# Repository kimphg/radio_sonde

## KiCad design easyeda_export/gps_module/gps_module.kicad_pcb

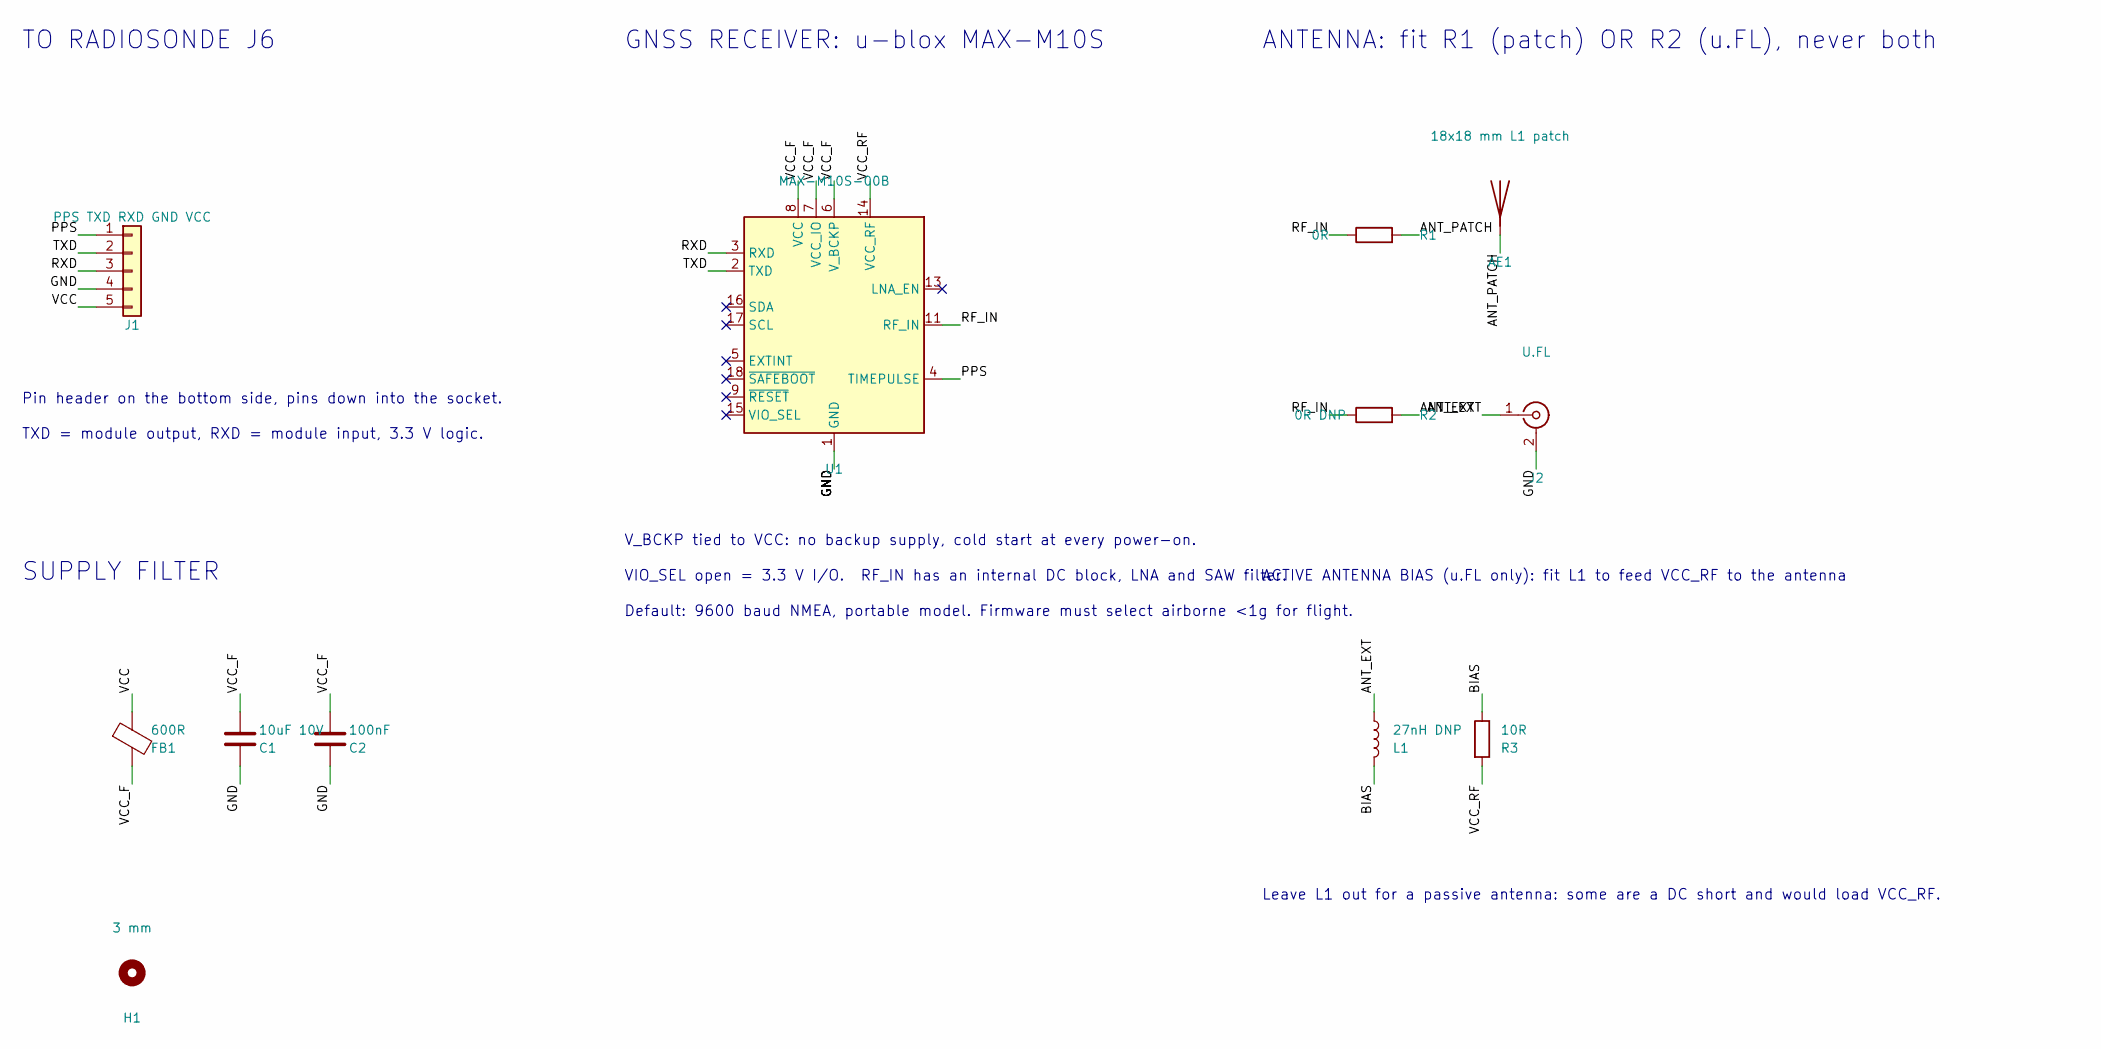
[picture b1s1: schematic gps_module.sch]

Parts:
AE1: 18x18 mm L1 patch; Patch_18x18_TH; MPN BWGNSCNX18-18W4; LCSC C784395
C1: 10uF 10V; C_0805_2012Metric; MPN CL21B106KOQNNNE; LCSC C95841
C2: 100nF; C_0603_1608Metric; MPN CL10B104KB8NNNC; LCSC C1591
FB1: 600R; L_0603_1608Metric; MPN BLM18AG601SN1D; LCSC C19330
H1: 3 mm; MountingHole_3mm
J1: PPS TXD RXD GND VCC; PinHeader_1x05_P2.54mm_Vertical
J2: U.FL; U.FL_Hirose_U.FL-R-SMT-1_Vertical; MPN U.FL-R-SMT-1(80); LCSC C88374
L1: 27nH DNP; L_0603_1608Metric
R1: 0R; R_0603_1608Metric
R2: 0R DNP; R_0603_1608Metric
R3: 10R; R_0603_1608Metric
U1: MAX-M10S-00B; ublox_MAX; MPN MAX-M10S-00B; LCSC C4153167

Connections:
ANT_EXT: J2.1 (In), L1.1, R2.2
ANT_PATCH: AE1.1, R1.2
BIAS: L1.2, R3.1
GND: C1.2, C2.2, J1.4, J2.2 (Ext), U1.1 (GND), U1.10 (GND), U1.12 (GND)
PPS: J1.1, U1.4 (TIMEPULSE)
RF_IN: R1.1, R2.1, U1.11 (RF_IN)
RXD: J1.3, U1.3 (RXD)
TXD: J1.2, U1.2 (TXD)
VCC: FB1.1, J1.5
VCC_F: C1.1, C2.1, FB1.2, U1.6 (V_BCKP), U1.7 (VCC_IO), U1.8 (VCC)
VCC_RF: R3.2, U1.14 (VCC_RF)

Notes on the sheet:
TO RADIOSONDE J6
Pin header on the bottom side, pins down into the socket.
TXD = module output, RXD = module input, 3.3 V logic.
SUPPLY FILTER
GNSS RECEIVER: u-blox MAX-M10S
V_BCKP tied to VCC: no backup supply, cold start at every power-on.
VIO_SEL open = 3.3 V I/O. RF_IN has an internal DC block, LNA and SAW filter.
Default: 9600 baud NMEA, portable model. Firmware must select airborne <1g for flight.
ANTENNA: fit R1 (patch) OR R2 (u.FL), never both
ACTIVE ANTENNA BIAS (u.FL only): fit L1 to feed VCC_RF to the antenna
Leave L1 out for a passive antenna: some are a DC short and would load VCC_RF.

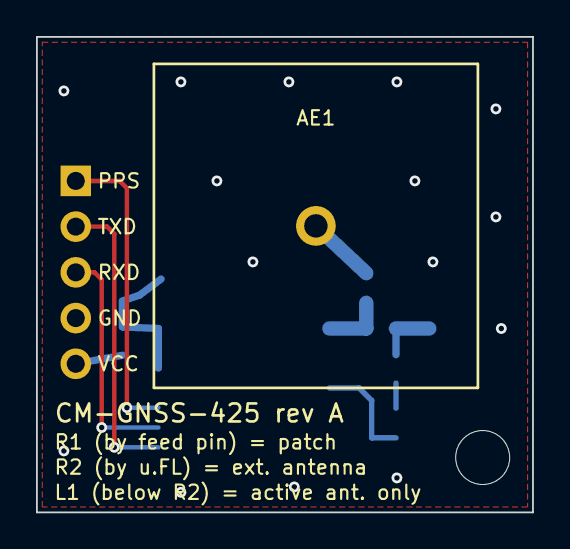
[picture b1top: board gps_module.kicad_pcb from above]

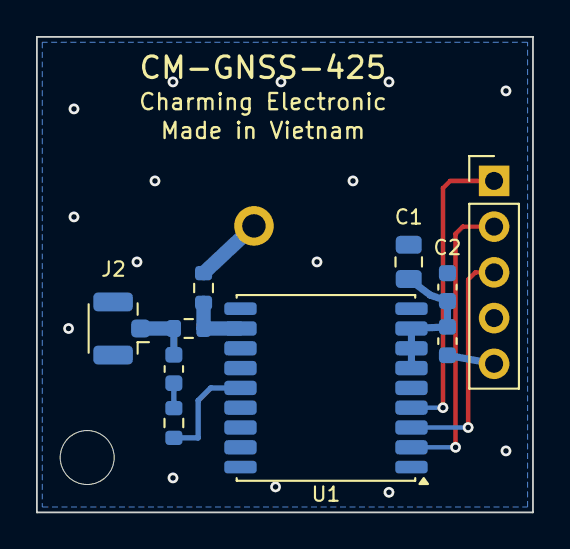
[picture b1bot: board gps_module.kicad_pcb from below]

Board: 2 copper layers, 27.6 x 26.4 mm, 12 parts (10 on the bottom side), 11 nets.

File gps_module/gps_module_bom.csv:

Designator,Quantity,Value,Footprint,LCSC Part Number,Manufacturer Part Number,Fit
U1,1,MAX-M10S-00B,ublox_MAX,C4153167,MAX-M10S-00B,yes
AE1,1,18x18x4 mm GPS L1 patch (through-hole pin),Patch_18x18_TH,C784395,BWGNSCNX18-18W4,yes (hand solder)
J1,1,Pin header 1x5 2.54 mm,PinHeader_1x05_P2.54mm_Vertical,,,yes (hand solder on bottom side)
J2,1,U.FL,U.FL_Hirose_U.FL-R-SMT-1,C88374,U.FL-R-SMT-1(80),yes
FB1,1,600R ferrite,0603,C19330,BLM18AG601SN1D,yes
C1,1,10uF 10V,0805,C95841,CL21B106KOQNNNE,yes
C2,1,100nF,0603,C1591,CL10B104KB8NNNC,yes
R1,1,0R,0603,,,yes (patch antenna selected)
R2,1,0R,0603,,,no (fit instead of R1 for u.FL)
R3,1,10R,0603,,,yes
L1,1,27nH,0603,,,no (fit only for an active antenna)

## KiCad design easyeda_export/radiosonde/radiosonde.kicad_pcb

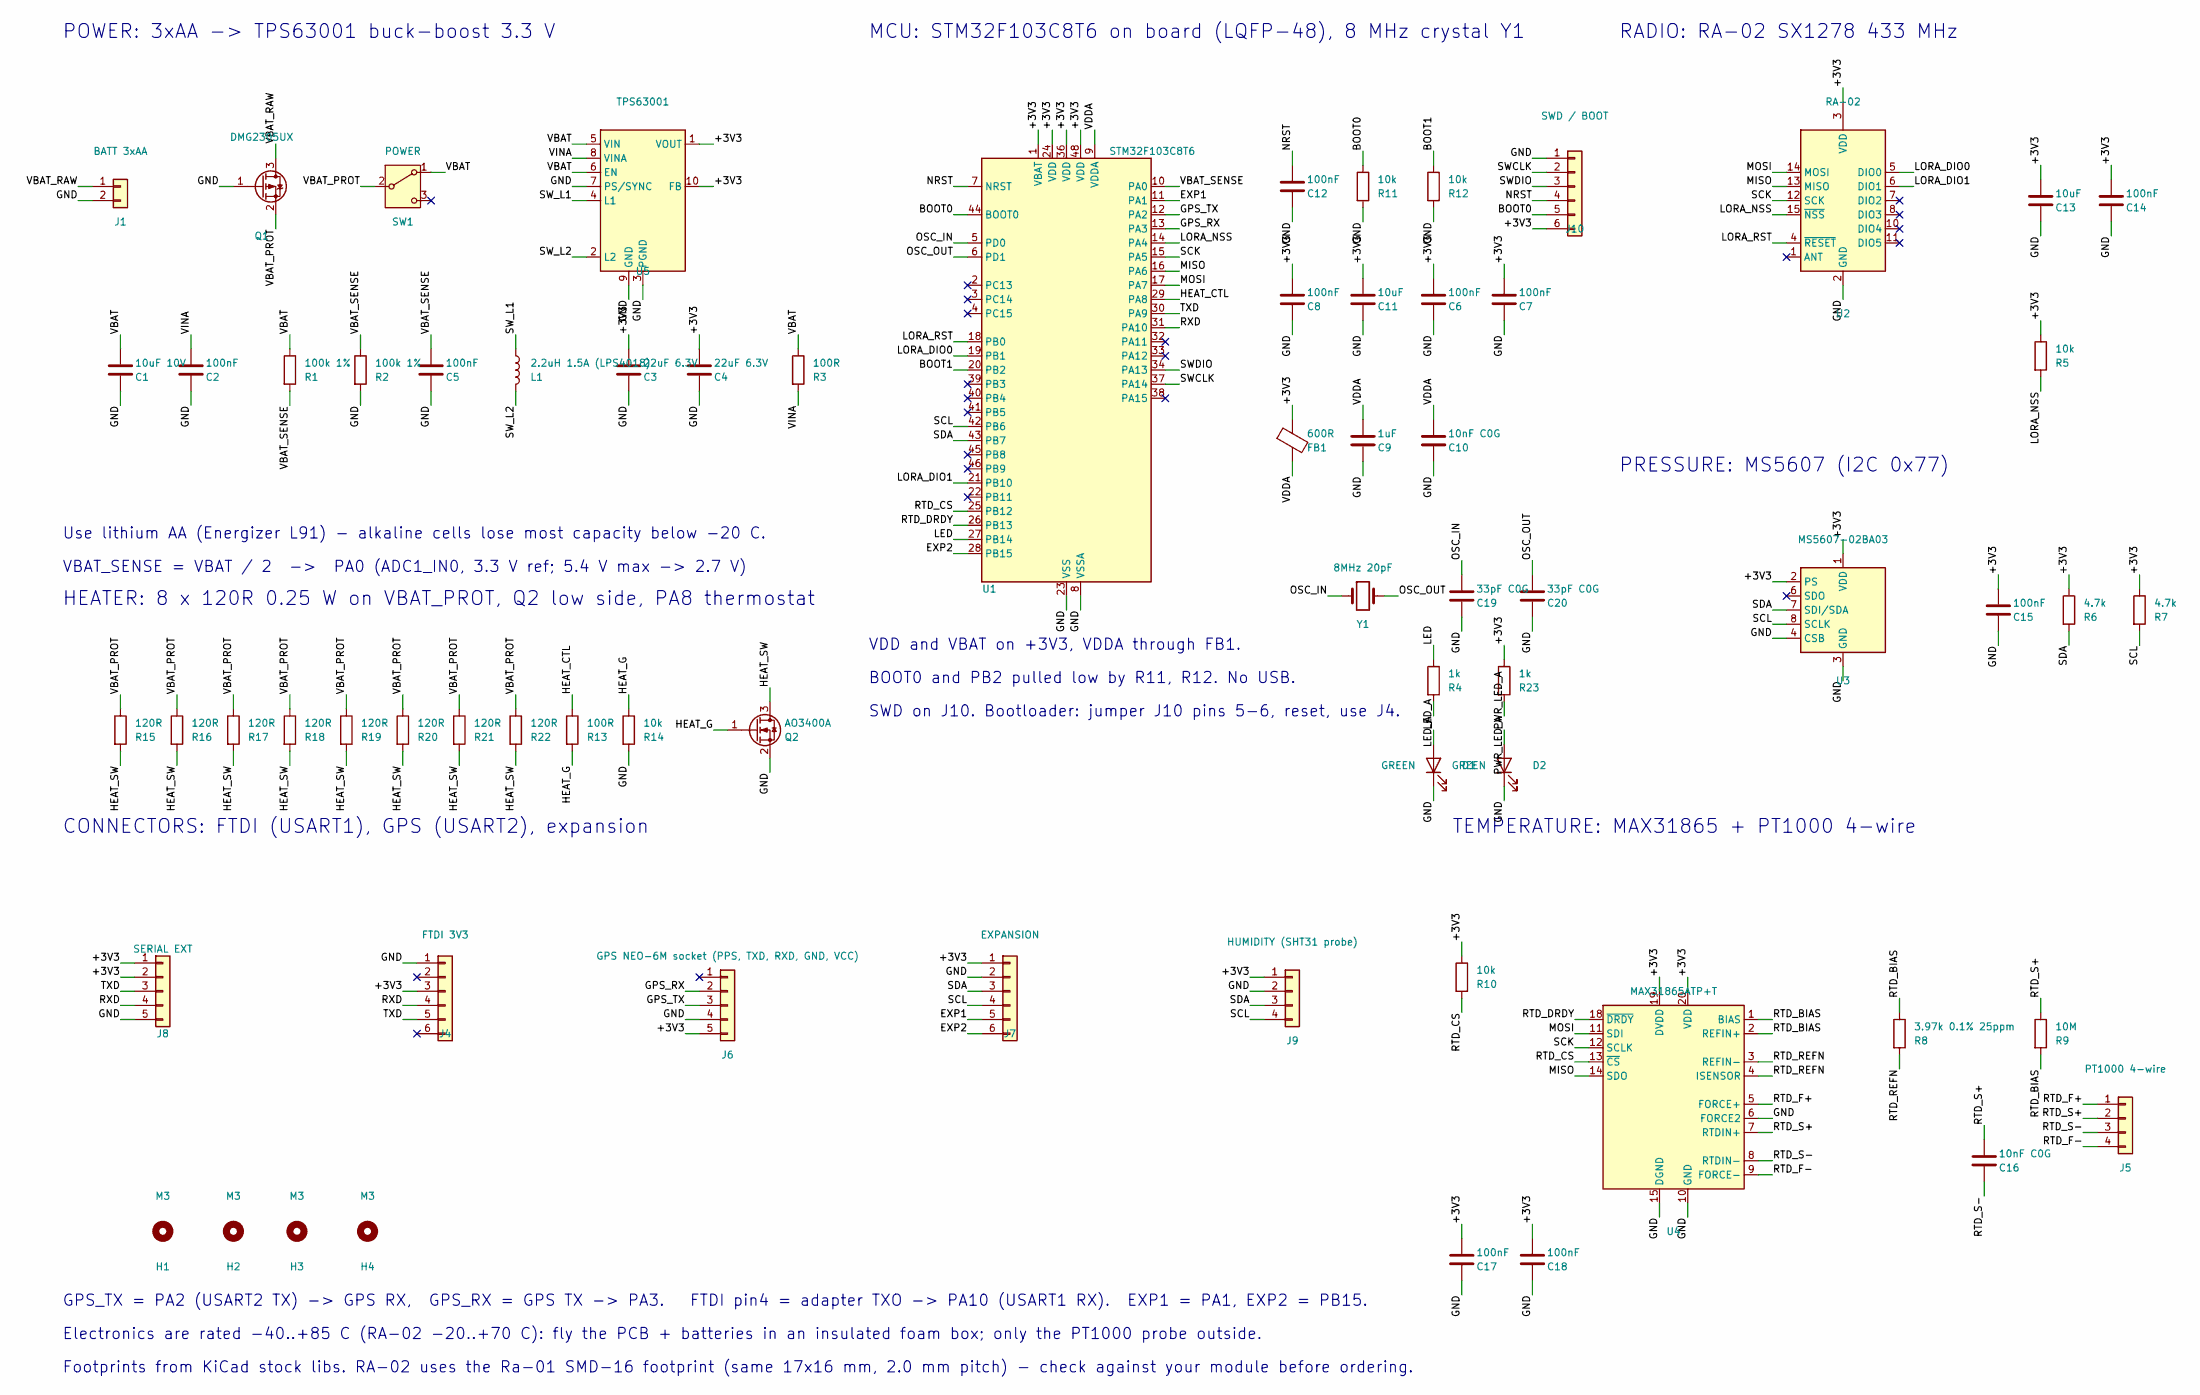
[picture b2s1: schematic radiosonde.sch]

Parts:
C1: 10uF 10V; C_0805_2012Metric; MPN CL21B106KOQNNNE; LCSC C95841
C2, C5, C6, C7, C8, C12, C14, C15, C17, C18: 100nF; C_0603_1608Metric; MPN CL10B104KB8NNNC; LCSC C1591
C3, C4: 22uF 6.3V; C_0805_2012Metric; MPN CL21A226MQQNNNE; LCSC C5674
C9: 1uF; C_0603_1608Metric; MPN CL10A105KB8NNNC; LCSC C15849
C10, C16: 10nF C0G; C_0603_1608Metric; MPN CGA3E1C0G2A103JT0Y0E; LCSC C432938
C11, C13: 10uF; C_0805_2012Metric; MPN CL21B106KOQNNNE; LCSC C95841
C19, C20: 33pF C0G; C_0603_1608Metric; MPN CL10C330JB8NNNC; LCSC C1663
D1, D2: GREEN; LED_0603_1608Metric; MPN 19-217/G7C-AN1P2/6T; LCSC C2986030
FB1: 600R; L_0603_1608Metric; MPN BLM18AG601SN1D; LCSC C19330
H1, H2, H3, H4: M3; MountingHole_3.2mm_M3
J1: BATT 3xAA; JST_PH_S2B-PH-K_1x02_P2.00mm_Horizontal; MPN S2B-PH-K-S(LF)(SN); LCSC C173752
J4: FTDI 3V3; PinHeader_1x06_P2.54mm_Vertical; MPN 2.54-1x6P; LCSC C37208
J5: PT1000 4-wire; JST_PH_B4B-PH-K_1x04_P2.00mm_Vertical; MPN B4B-PH-K-S(LF)(SN); LCSC C131334
J6: GPS NEO-6M socket (PPS, TXD, RXD, GND, VCC); GPS_NEO6M_5pin; MPN DS1023-1x5SF11; LCSC C7509517
J7: EXPANSION; PinHeader_1x06_P2.54mm_Vertical; MPN 2.54-1x6P; LCSC C37208
J8: SERIAL EXT; PinHeader_1x05_P2.54mm_Vertical
J9: HUMIDITY (SHT31 probe); JST_PH_B4B-PH-K_1x04_P2.00mm_Vertical; MPN B4B-PH-K-S(LF)(SN); LCSC C131334
J10: SWD / BOOT; PinHeader_1x06_P2.54mm_Vertical; MPN 2.54-1x6P; LCSC C37208
L1: 2.2uH 1.5A (LPS4018); L_Coilcraft_LPS4018; MPN LPS4018-222MRC; LCSC C4354938
Q1: DMG2305UX; SOT-23; MPN DMG2305UX-7; LCSC C150470
Q2: AO3400A; SOT-23; MPN AO3400A; LCSC C20917
R1, R2: 100k 1%; R_0603_1608Metric; MPN 0603WAF1003T5E; LCSC C25803
R3, R13: 100R; R_0603_1608Metric; MPN 0603WAF1000T5E; LCSC C22775
R4, R23: 1k; R_0603_1608Metric; MPN 0603WAF1001T5E; LCSC C21190
R5, R10, R11, R12, R14: 10k; R_0603_1608Metric; MPN 0603WAF1002T5E; LCSC C25804
R6, R7: 4.7k; R_0603_1608Metric; MPN 0603WAF4701T5E; LCSC C23162
R8: 3.97k 0.1% 25ppm; R_0603_1608Metric; MPN RT0603BRD073K97L; LCSC C861386
R9: 10M; R_0603_1608Metric; MPN 0603WAF1005T5E; LCSC C7250
R15, R16, R17, R18, R19, R20, R21, R22: 120R; R_1206_3216Metric; MPN 1206W4F1200T5E; LCSC C17909
SW1: POWER; SW_SPDT_PCM12; MPN PCM12SMTR; LCSC C221841
U1: STM32F103C8T6; LQFP-48_7x7mm_P0.5mm; MPN STM32F103C8T6; LCSC C8734
U2: RA-02; Ai-Thinker-Ra-01-LoRa; MPN Ra-02; LCSC C90039
U3: MS5607-02BA03; LGA-8_3x5mm_P1.25mm; MPN MS560702BA03-50; LCSC C97627
U4: MAX31865ATP+T; TQFN-20-1EP_5x5mm_P0.65mm_EP3.25x3.25mm_Vias0.3mm; MPN MAX31865ATP+T; LCSC C118474
U5: TPS63001; Texas_DRC0010J_ThermalVias_0.3mm; MPN TPS63001DRCR; LCSC C28060
Y1: 8MHz 20pF; Crystal_SMD_5032-2Pin_5.0x3.2mm; MPN X50328MSB2GI; LCSC C115962

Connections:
+3V3: C3.1, C4.1, C6.1, C7.1, C8.1, C11.1, C13.1, C14.1, C15.1, C17.1, C18.1, FB1.1, J4.3, J6.5, J7.1, J8.1, J8.2, J9.1, J10.6, R5.1, R6.1, R7.1, R10.1, R23.1, U1.1 (VBAT), U1.24 (VDD), U1.36 (VDD), U1.48 (VDD), U2.3 (VDD), U3.1 (VDD), U3.2 (PS), U4.19 (DVDD), U4.20 (VDD), U5.1 (VOUT), U5.10 (FB)
BOOT0: J10.5, R11.1, U1.44 (BOOT0)
BOOT1: R12.1, U1.20 (PB2)
EXP1: J7.5, U1.11 (PA1)
EXP2: J7.6, U1.28 (PB15)
GND: C1.2, C2.2, C3.2, C4.2, C5.2, C6.2, C7.2, C8.2, C9.2, C10.2, C11.2, C12.2, C13.2, C14.2, C15.2, C17.2, C18.2, C19.2, C20.2, D1.1 (K), D2.1 (K), J1.2, J4.1, J6.4, J7.2, J8.5, J9.2, J10.1, Q1.1 (G), Q2.2 (S), R2.2, R11.2, R12.2, R14.2, U1.8 (VSSA), U1.23 (VSS), U1.35 (VSS), U1.47 (VSS), U2.2 (GND), U2.9 (GND), U2.16 (GND), U3.3 (GND), U3.4 (CSB), U3.5 (CSB), U4.6 (FORCE2), U4.10 (GND), U4.15 (DGND), U4.16 (GND), U4.21 (GND), U5.3 (PGND), U5.7 (PS/SYNC), U5.9 (GND), U5.11 (PGND)
GPS_RX: J6.2, U1.13 (PA3)
GPS_TX: J6.3, U1.12 (PA2)
HEAT_CTL: R13.1, U1.29 (PA8)
HEAT_G: Q2.1 (G), R13.2, R14.1
HEAT_SW: Q2.3 (D), R15.2, R16.2, R17.2, R18.2, R19.2, R20.2, R21.2, R22.2
LED: R4.1, U1.27 (PB14)
LED_A: D1.2 (A), R4.2
LORA_DIO0: U1.19 (PB1), U2.5 (DIO0)
LORA_DIO1: U1.21 (PB10), U2.6 (DIO1)
LORA_NSS: R5.2, U1.14 (PA4), U2.15 (~NSS)
LORA_RST: U1.18 (PB0), U2.4 (~RESET)
MISO: U1.16 (PA6), U2.13 (MISO), U4.14 (SDO)
MOSI: U1.17 (PA7), U2.14 (MOSI), U4.11 (SDI)
NRST: C12.1, J10.4, U1.7 (NRST)
OSC_IN: C19.1, U1.5 (PD0), Y1.1
OSC_OUT: C20.1, U1.6 (PD1), Y1.2
PWR_LED_A: D2.2 (A), R23.2
RTD_BIAS: R8.1, R9.2, U4.1 (BIAS), U4.2 (REFIN+)
RTD_CS: R10.2, U1.25 (PB12), U4.13 (~CS)
RTD_DRDY: U1.26 (PB13), U4.18 (~DRDY)
RTD_F+: J5.1, U4.5 (FORCE+)
RTD_F-: J5.4, U4.9 (FORCE-)
RTD_REFN: R8.2, U4.3 (REFIN-), U4.4 (ISENSOR)
RTD_S+: C16.1, J5.2, R9.1, U4.7 (RTDIN+)
RTD_S-: C16.2, J5.3, U4.8 (RTDIN-)
RXD: J4.4, J8.4, U1.31 (PA10)
SCK: U1.15 (PA5), U2.12 (SCK), U4.12 (SCLK)
SCL: J7.4, J9.4, R7.2, U1.42 (PB6), U3.8 (SCLK)
SDA: J7.3, J9.3, R6.2, U1.43 (PB7), U3.7 (SDI/SDA)
SWCLK: J10.2, U1.37 (PA14)
SWDIO: J10.3, U1.34 (PA13)
SW_L1: L1.1, U5.4 (L1)
SW_L2: L1.2, U5.2 (L2)
TXD: J4.5, J8.3, U1.30 (PA9)
VBAT: C1.1, R1.1, R3.1, SW1.1 (A), U5.5 (VIN), U5.6 (EN)
VBAT_PROT: Q1.2 (S), R15.1, R16.1, R17.1, R18.1, R19.1, R20.1, R21.1, R22.1, SW1.2 (B)
VBAT_RAW: J1.1, Q1.3 (D)
VBAT_SENSE: C5.1, R1.2, R2.1, U1.10 (PA0)
VDDA: C9.1, C10.1, FB1.2, U1.9 (VDDA)
VINA: C2.1, R3.2, U5.8 (VINA)

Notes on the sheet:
GPS_TX = PA2 (USART2 TX) -> GPS RX, GPS_RX = GPS TX -> PA3. FTDI pin4 = adapter TXO -> PA10 (USART1 RX). EXP1 = PA1, EXP2 = PB15.
POWER: 3xAA -> TPS63001 buck-boost 3.3 V
VBAT_SENSE = VBAT / 2 -> PA0 (ADC1_IN0, 3.3 V ref; 5.4 V max -> 2.7 V)
Footprints from KiCad stock libs. RA-02 uses the Ra-01 SMD-16 footprint (same 17x16 mm, 2.0 mm pitch) - check against your module before ordering.
RADIO: RA-02 SX1278 433 MHz
Use lithium AA (Energizer L91) - alkaline cells lose most capacity below -20 C.
SWD on J10. Bootloader: jumper J10 pins 5-6, reset, use J4.
Electronics are rated -40..+85 C (RA-02 -20..+70 C): fly the PCB + batteries in an insulated foam box; only the PT1000 probe outside.
CONNECTORS: FTDI (USART1), GPS (USART2), expansion
HEATER: 8 x 120R 0.25 W on VBAT_PROT, Q2 low side, PA8 thermostat
PRESSURE: MS5607 (I2C 0x77)
MCU: STM32F103C8T6 on board (LQFP-48), 8 MHz crystal Y1
TEMPERATURE: MAX31865 + PT1000 4-wire
VDD and VBAT on +3V3, VDDA through FB1.
BOOT0 and PB2 pulled low by R11, R12. No USB.

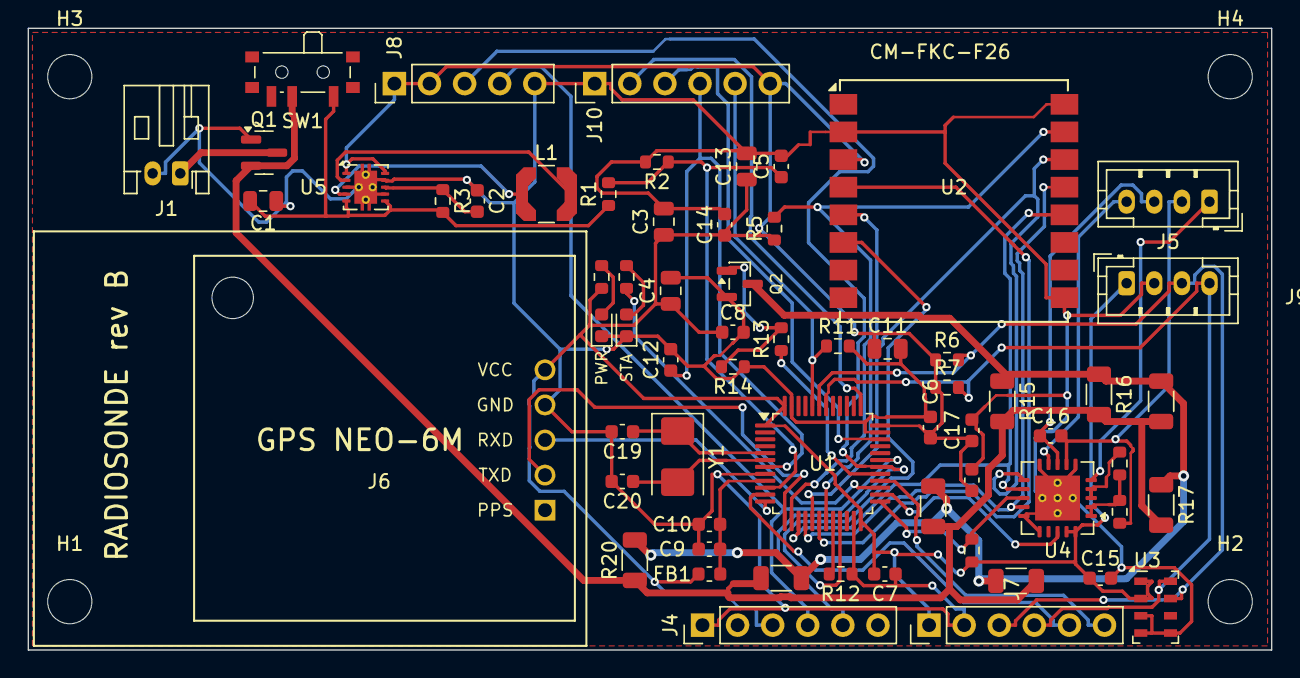
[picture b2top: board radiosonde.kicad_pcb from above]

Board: 2 copper layers, 90.0 x 45.0 mm, 68 parts (0 on the bottom side), 46 nets.

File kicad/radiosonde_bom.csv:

Designator,Quantity,Value,LCSC Part Number,Manufacturer Part Number
"C1,C11,C13",3,10uF 10V / 10uF,C95841,CL21B106KOQNNNE
"C10,C16",2,10nF C0G,C432938,CGA3E1C0G2A103JT0Y0E
"C19,C20",2,33pF C0G,C1663,CL10C330JB8NNNC
"C2,C5,C6,C7,C8,C12,C14,C15,C17,C18",10,100nF,C1591,CL10B104KB8NNNC
"C3,C4",2,22uF 6.3V,C5674,CL21A226MQQNNNE
C9,1,1uF,C15849,CL10A105KB8NNNC
"D1,D2",2,GREEN,C2986030,19-217/G7C-AN1P2/6T
FB1,1,600R,C19330,BLM18AG601SN1D
J1,1,BATT 3xAA,C173752,S2B-PH-K-S(LF)(SN)
"J4,J7,J10",3,FTDI 3V3 / EXPANSION / SWD / BOOT,C37208,2.54-1x6P
"J5,J9",2,PT1000 4-wire / HUMIDITY (SHT31 probe),C131334,B4B-PH-K-S(LF)(SN)
J6,1,"GPS NEO-6M socket (PPS, TXD, RXD, GND, VCC)",C7509517,DS1023-1x5SF11
L1,1,2.2uH 1.5A (LPS4018),C4354938,LPS4018-222MRC
Q1,1,DMG2305UX,C150470,DMG2305UX-7
Q2,1,AO3400A,C20917,AO3400A
"R1,R2",2,100k 1%,C25803,0603WAF1003T5E
"R15,R16,R17,R18,R19,R20,R21,R22",8,120R,C17909,1206W4F1200T5E
"R3,R13",2,100R,C22775,0603WAF1000T5E
"R4,R23",2,1k,C21190,0603WAF1001T5E
"R5,R10,R11,R12,R14",5,10k,C25804,0603WAF1002T5E
"R6,R7",2,4.7k,C23162,0603WAF4701T5E
R8,1,3.97k 0.1% 25ppm,C861386,RT0603BRD073K97L
R9,1,10M,C7250,0603WAF1005T5E
SW1,1,POWER,C221841,PCM12SMTR
U1,1,STM32F103C8T6,C8734,STM32F103C8T6
U2,1,RA-02,C90039,Ra-02
U3,1,MS5607-02BA03,C97627,MS560702BA03-50
U4,1,MAX31865ATP+T,C118474,MAX31865ATP+T
U5,1,TPS63001,C28060,TPS63001DRCR
Y1,1,8MHz 20pF,C115962,X50328MSB2GI

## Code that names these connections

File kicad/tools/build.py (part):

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
RA02 = make_ra02()

BP_ROW1 = ['PB12','PB13','PB14','PB15','PA8','PA9','PA10','PA11','PA12','PA15','PB3','PB4','PB5','PB6','PB7','PB8','PB9','5V','GND','3V3']
BP_ROW2 = ['VBAT','PC13','PC14','PC15','PA0','PA1','PA2','PA3','PA4','PA5','PA6','PA7','PB0','PB1','PB10','PB11','NRST','3V3','GND','GND']
def make_bluepill():
    def pin(num, name, x, ang, y):
        t = {'3V3': 'power_in', 'GND': 'power_in', '5V': 'passive', 'VBAT': 'passive', 'NRST': 'passive'}.get(name, 'bidirectional')
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    return ['symbol', S('BluePill'), ['in_bom', 'yes'], ['on_board', 'yes'],
            pr('Reference', 'U', 29.21), pr('Value', 'BluePill', -29.21),
            pr('Footprint', 'radiosonde:BluePill_Socket', 0, True), pr('Datasheet', '~', 0, True),
            pr('Description', 'STM32F103C8T6 Blue Pill board in 2x20 female headers (pin 1 = PB12, pin 21 = VBAT, both at USB end)', 0, True),
            ['symbol', S('BluePill_0_1'), ['rectangle', ['start', -12.7, 27.94], ['end', 12.7, -27.94],
                ['stroke', ['width', 0.254], ['type', 'default']], ['fill', ['type', 'background']]]],
            ['symbol', S('BluePill_1_1')] + ps]
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def write_bluepill_fp(out):
    os.makedirs(f'{out}/radiosonde.pretty', exist_ok=True)
    L = ['(footprint "BluePill_Socket" (version 20221018) (generator pcbnew) (layer "F.Cu")',
         '  (descr "STM32 Blue Pill in 2x20 2.54 mm female headers, rows 15.24 mm apart. Top view, USB at left. Pin 1 = PB12, pin 21 = VBAT.")',
         '  (attr through_hole)',
         '  (fp_text reference "REF**" (at 24.13 -12.7) (layer "F.SilkS") (effects (font (size 1 1) (thickness 0.15))))',
         '  (fp_text value "BluePill" (at 24.13 12.7) (layer "F.Fab") (effects (font (size 1 1) (thickness 0.15))))',
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part('#FLG1', 'power', 'PWR_FLAG', 'PWR_FLAG', '', 43.18, 104.14, {'1': 'VBAT'})
part('#FLG2', 'power', 'PWR_FLAG', 'PWR_FLAG', '', 55.88, 104.14, {'1': 'GND'})
note(20, 112, 'Use lithium AA (Energizer L91) - alkaline cells lose most capacity below -20 C.')
note(20, 118, 'VBAT_SENSE = VBAT / 2  ->  PA0 (ADC1_IN0, 3.3 V ref; 5.4 V max -> 2.7 V)')

# ===== MCU =====
note(165, 22, 'MCU: STM32F103C8T6 Blue Pill (plug-in, 2x20 female headers)', 2.5)
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     {'1': '+3V3', '2': 'GND', '3': 'SDA', '4': 'SCL', '5': 'EXP1', '6': 'EXP2'})
part('H1', 'Mechanical', 'MountingHole', 'M3', 'MountingHole:MountingHole_3.2mm_M3', 38.1, 236.22, {})
part('H2', 'Mechanical', 'MountingHole', 'M3', 'MountingHole:MountingHole_3.2mm_M3', 50.8, 236.22, {})
note(20, 250, 'GPS_TX = PA2 (USART2 TX) -> GPS RX,  GPS_RX = GPS TX -> PA3.   FTDI pin4 = adapter TXO -> PA10 (USART1 RX).  EXP1 = PA1, EXP2 = PB15.')
note(20, 256, 'Electronics are rated -40..+85 C (RA-02 -20..+70 C, Blue Pill clones untested in cold): fly the PCB + batteries in an insulated foam box; only the PT1000 probe outside.')
note(20, 262, 'Footprints from KiCad stock libs. RA-02 uses the Ra-01 SMD-16 footprint (same 17x16 mm, 2.0 mm pitch) - check against your module before ordering.')

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
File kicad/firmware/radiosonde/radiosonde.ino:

// Radiosonde firmware - on-board STM32F103C8T6, 8 MHz crystal (STM32duino core: board "Generic STM32F1 series", part "BluePill F103C8")
// Upload via ST-Link (SWD) or USART1 bootloader. Libraries: LoRa (Sandeep Mistry), TinyGPSPlus (Mikal Hart)
#include <SPI.h>
#include <Wire.h>
#include <LoRa.h>
#include <TinyGPSPlus.h>

// ---- pin map (matches schematic) ----
const uint32_t PIN_LORA_NSS = PA4;
const uint32_t PIN_LORA_RST = PB0;
const uint32_t PIN_LORA_DIO0 = PB1;
const uint32_t PIN_RTD_CS = PB12;
const uint32_t PIN_RTD_DRDY = PB13;
const uint32_t PIN_LED = PB14;
const uint32_t PIN_VBAT = PA0;      // divider 100k/100k
const uint32_t PIN_HEATER = PA8;    // HIGH turns on R15-R22 through Q2
// SPI1 = PA5/PA6/PA7, I2C1 = PB6 (SCL) / PB7 (SDA)

const long LORA_FREQ = 434000000L;  // 433.05-434.79 MHz SRD band - check local rules
const float RREF = 3970.0f, R0 = 1000.0f;  // R8; the fault thresholds in maxInit() depend on this value
const uint8_t MS5607_ADDR = 0x77;   // CSB = GND
const uint8_t SHT31_ADDR = 0x44;    // external probe on J9, ADDR pin low
const float HEAT_ON_C = 10.0f, HEAT_OFF_C = 15.0f;  // board temperature band, starts early because the heater can't keep up at 15 km
const float HEAT_MIN_VBAT = 3.0f;  // 1.0 V per cell; below this the heater stays off until reset, so the radio keeps running

HardwareSerial gpsSerial(PA3, PA2);   // USART2: RX=PA3 <- GPS TX, TX=PA2 -> GPS RX
HardwareSerial dbg(PA10, PA9);        // USART1 debug / bootloader (J4)
TinyGPSPlus gps;
uint16_t msC[8];
uint32_t frame = 0;
bool heaterOn = false, heaterLocked = false;

// ---------------- MAX31865 ----------------
SPISettings maxSPI(1000000, MSBFIRST, SPI_MODE1);
void maxWrite(uint8_t reg, uint8_t v) {
  SPI.beginTransaction(maxSPI); digitalWrite(PIN_RTD_CS, LOW);
  SPI.transfer(reg | 0x80); SPI.transfer(v);
  digitalWrite(PIN_RTD_CS, HIGH); SPI.endTransaction();
}
void maxRead(uint8_t reg, uint8_t *b, uint8_t n) {
  SPI.beginTransaction(maxSPI); digitalWrite(PIN_RTD_CS, LOW);
  SPI.transfer(reg & 0x7F);
  while (n--) *b++ = SPI.transfer(0);
  digitalWrite(PIN_RTD_CS, HIGH); SPI.endTransaction();
}
void maxInit() {
  maxWrite(0x03, 0x56); maxWrite(0x04, 0xDE);  // high fault ~ +90 C
  maxWrite(0x05, 0x2E); maxWrite(0x06, 0xA8);  // low fault  ~ -70 C
  maxWrite(0x00, 0xC3);                        // VBIAS, auto, 4-wire, clear, 50 Hz
}
float rtdTemp() {  // NAN on fault
  uint8_t d[2]; maxRead(0x01, d, 2);
  if (d[1] & 1) { maxWrite(0x00, 0xC3); return NAN; }
  uint16_t code = ((uint16_t)d[0] << 8 | d[1]) >> 1;
  float r = code * RREF / 32768.0f;
  const float A = 3.9083e-3f, B = -5.775e-7f;
  return (-A + sqrt(A * A - 4.0f * B * (1.0f - r / R0))) / (2.0f * B);
}

// ---------------- MS5607 ----------------
void msCmd(uint8_t c) { Wire.beginTransmission(MS5607_ADDR); Wire.write(c); Wire.endTransmission(); }
uint32_t msAdc(uint8_t conv) {
  msCmd(conv); delay(10);
  msCmd(0x00); Wire.requestFrom(MS5607_ADDR, (uint8_t)3);
  uint32_t v = 0; for (uint8_t i = 0; i < 3; i++) v = (v << 8) | Wire.read();
  return v;
}
void msInit() {
  msCmd(0x1E); delay(5);
  for (uint8_t i = 0; i < 8; i++) {
    msCmd(0xA0 + 2 * i); Wire.requestFrom(MS5607_ADDR, (uint8_t)2);
    msC[i] = (uint16_t)Wire.read() << 8 | Wire.read();
  }
}
void msRead(float &p_hPa, float &t_C) {
  uint32_t D1 = msAdc(0x48), D2 = msAdc(0x58);  // OSR 4096
  int32_t dT = (int32_t)D2 - ((int32_t)msC[5] << 8);
  int32_t TEMP = 2000 + (int64_t)dT * msC[6] / 8388608LL;
  int64_t OFF = ((int64_t)msC[2] << 17) + ((int64_t)msC[4] * dT) / 64;
  int64_t SENS = ((int64_t)msC[1] << 16) + ((int64_t)msC[3] * dT) / 128;
  if (TEMP < 2000) {  // 2nd-order compensation (MS5607 datasheet)
    int64_t T2 = ((int64_t)dT * dT) >> 31, t = TEMP - 2000;
    int64_t OFF2 = 61 * t * t / 16, SENS2 = 2 * t * t;
    if (TEMP < -1500) { int64_t u = TEMP + 1500; OFF2 += 15 * u * u; SENS2 += 8 * u * u; }
    TEMP -= T2; OFF -= OFF2; SENS -= SENS2;
  }
  int32_t P = (((int64_t)D1 * SENS >> 21) - OFF) >> 15;  // 0.01 mbar
  p_hPa = P / 100.0f; t_C = TEMP / 100.0f;
}
float baroAlt(float p) {  // ISA, valid to 20 km
  if (p > 226.321f) return 44330.8f * (1.0f - pow(p / 1013.25f, 0.190263f));
  return 11000.0f - 6341.6f * log(p / 226.321f);
}

// ---------------- SHT31 humidity probe ----------------
uint8_t shtCrc(const uint8_t *d, uint8_t n) {  // polynomial 0x31, init 0xFF
  uint8_t crc = 0xFF;
  while (n--) {
    crc ^= *d++;
    for (uint8_t i = 0; i < 8; i++) crc = (crc & 0x80) ? (crc << 1) ^ 0x31 : crc << 1;
  }
  return crc;
}
void shtRead(float &rh, float &t_C) {  // both NAN if the probe is missing or the data is corrupt
  rh = NAN; t_C = NAN;
  Wire.beginTransmission(SHT31_ADDR); Wire.write(0x24); Wire.write(0x00);  // single shot, high repeatability
  if (Wire.endTransmission() != 0) return;
  delay(20);
  if (Wire.requestFrom(SHT31_ADDR, (uint8_t)6) != 6) return;
  uint8_t d[6]; for (uint8_t i = 0; i < 6; i++) d[i] = Wire.read();
  if (shtCrc(d, 2) != d[2] || shtCrc(d + 3, 2) != d[5]) return;
  t_C = -45.0f + 175.0f * ((uint16_t)d[0] << 8 | d[1]) / 65535.0f;
  rh = 100.0f * ((uint16_t)d[3] << 8 | d[4]) / 65535.0f;
}

// ---------------- GPS: u-blox airborne <1g mode (required above 18 km, recommended always) ----------------
const uint8_t UBX_AIRBORNE[] = {0xB5,0x62,0x06,0x24,0x24,0x00,0xFF,0xFF,0x06,0x03,0x00,0x00,0x00,0x00,0x10,0x27,0x00,0x00,
  0x05,0x00,0xFA,0x00,0xFA,0x00,0x64,0x00,0x2C,0x01,0x00,0x00,0x00,0x00,0x00,0x00,0x00,0x00,0x00,0x00,0x00,0x00,0x00,0x00,0x16,0xDC};

float vbat() {
  uint32_t s = 0; for (uint8_t i = 0; i < 8; i++) s += analogRead(PIN_VBAT);
  return (s / 8.0f) * 3.3f / 4095.0f * 2.0f;  // calibrate per board
}

void heaterUpdate(float t_board, float vb) {
  if (vb < HEAT_MIN_VBAT) heaterLocked = true;
  if (heaterLocked || isnan(t_board) || t_board < -60.0f || t_board > 85.0f) heaterOn = false;
  else if (t_board < HEAT_ON_C) heaterOn = true;
  else if (t_board > HEAT_OFF_C) heaterOn = false;
  digitalWrite(PIN_HEATER, heaterOn ? HIGH : LOW);
}

void setup() {
  digitalWrite(PIN_HEATER, LOW); pinMode(PIN_HEATER, OUTPUT);
  pinMode(PIN_LED, OUTPUT); pinMode(PIN_RTD_CS, OUTPUT); digitalWrite(PIN_RTD_CS, HIGH);
  dbg.begin(115200);
  analogReadResolution(12);
  SPI.begin();
  Wire.setSDA(PB7); Wire.setSCL(PB6); Wire.begin(); Wire.setClock(100000);  // 100 kHz: the bus runs down the J9 probe cable
  maxInit(); msInit();
  gpsSerial.begin(9600);
  gpsSerial.write(UBX_AIRBORNE, sizeof(UBX_AIRBORNE));
  LoRa.setPins(PIN_LORA_NSS, PIN_LORA_RST, PIN_LORA_DIO0);
  if (!LoRa.begin(LORA_FREQ)) { while (1) { digitalWrite(PIN_LED, !digitalRead(PIN_LED)); delay(100); } }
  LoRa.setSpreadingFactor(9); LoRa.setSignalBandwidth(125E3); LoRa.setCodingRate4(5);
  LoRa.setTxPower(17, PA_OUTPUT_PA_BOOST_PIN); LoRa.enableCrc();
}

void loop() {
  uint32_t t0 = millis();
  while (millis() - t0 < 900) while (gpsSerial.available()) gps.encode(gpsSerial.read());

  float p, tint; msRead(p, tint);
  float tair = rtdTemp(), vb = vbat();
  heaterUpdate(tint, vb);
  float rh, trh; shtRead(rh, trh);
  char buf[140];
  // frame,lat,lon,gps_alt,press_hPa,baro_alt,t_air,t_board,vbat,sats,rh,t_rh,heat   (Arduino IDE: Tools > C Runtime Library > "Newlib Nano + Float Printf")
  snprintf(buf, sizeof(buf), "$RS,%lu,%.6f,%.6f,%.0f,%.2f,%.0f,%.2f,%.1f,%.2f,%d,%.1f,%.1f,%d", (unsigned long)frame++,
           gps.location.lat(), gps.location.lng(), gps.altitude.meters(), p, baroAlt(p), tair, tint, vb, (int)gps.satellites.value(), rh, trh, heaterOn ? 1 : 0);

  digitalWrite(PIN_LED, HIGH);
  LoRa.beginPacket(); LoRa.print(buf); LoRa.endPacket();
  digitalWrite(PIN_LED, LOW);
  dbg.println(buf);
}
